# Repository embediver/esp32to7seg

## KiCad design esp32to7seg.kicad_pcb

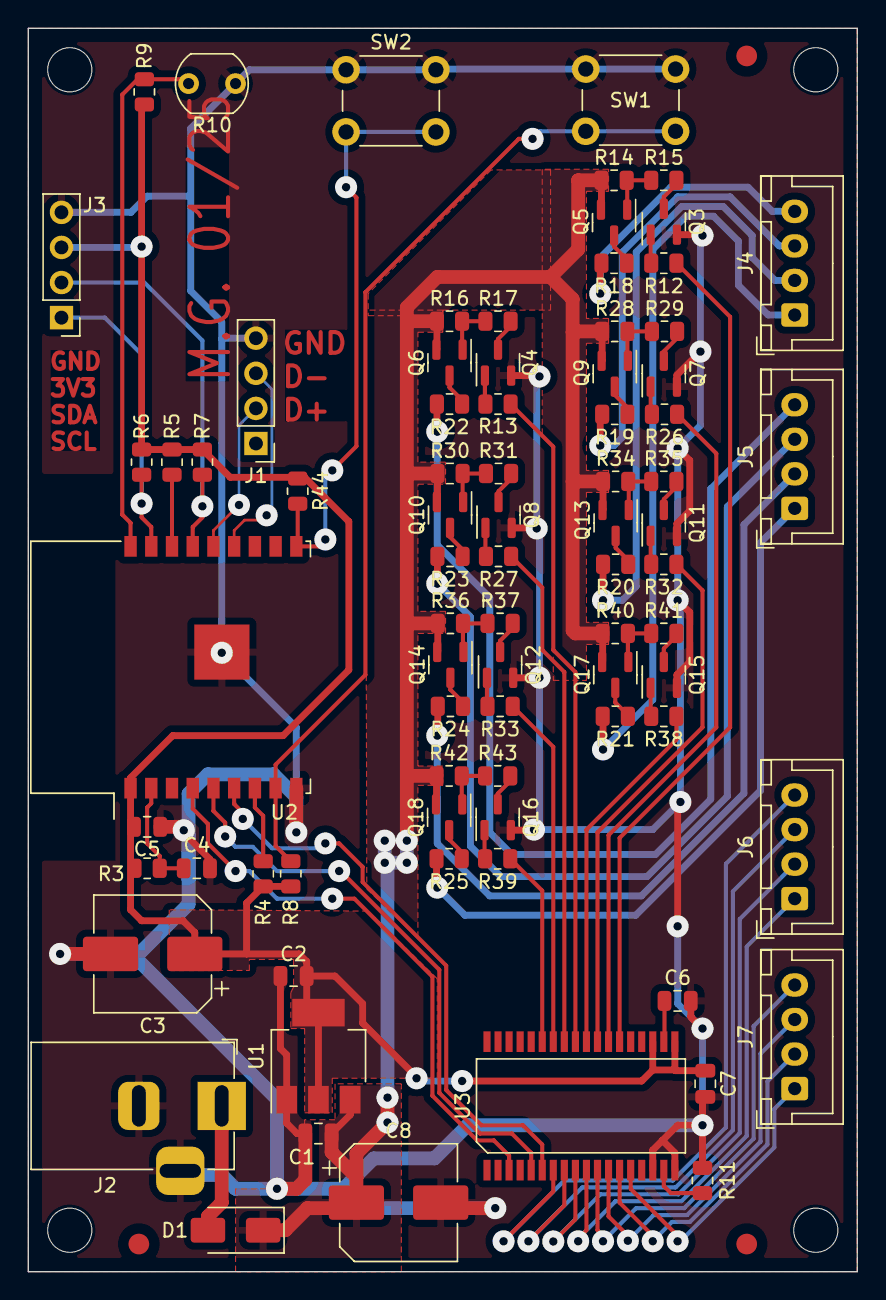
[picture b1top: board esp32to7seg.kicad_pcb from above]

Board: 2 copper layers, 60.0 x 90.0 mm, 86 parts (0 on the bottom side), 75 nets.

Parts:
C1, C2, C5, C7: 100n; C_0805_2012Metric
C3, C8: 220u; CP_Elec_8x6.2
C4: 1u; C_0805_2012Metric
C6: 22p; C_0805_2012Metric
D1: D_Schottky; D_SMA
FID1, FID2, FID3: Fiducial; Fiducial_1.5mm_Mask3mm
H1, H2, H3, H4: MountingHole; MountingHole_3.2mm_M3_DIN965
J1: Conn_01x04_Pin; PinHeader_1x04_P2.54mm_Vertical
J2: Barrel_Jack_Switch; BarrelJack_Horizontal
J3: Conn_01x04; PinHeader_1x04_P2.54mm_Vertical
J4, J5, J6, J7: Conn_01x04_Pin; JST_XH_B4B-XH-A_1x04_P2.50mm_Vertical
Q3, Q4, Q7, Q8, Q11, Q12, Q15, Q16: BC817; SOT-23
Q5, Q6, Q9, Q10, Q13, Q14, Q17, Q18: BC807; SOT-23
R3, R4, R5, R6, R7, R8, R12, R13, R14, R16, R26, R27, R28, R30, R32, R33, R34, R36, R38, R39, R40, R42, R44: 10k; R_0805_2012Metric
R9: tbd; R_0805_2012Metric
R10: LDR07; R_LDR_5.1x4.3mm_P3.4mm_Vertical
R11: 56k; R_0805_2012Metric
R15, R17, R29, R31, R35, R37, R41, R43: 1k; R_0805_2012Metric
R18, R19, R20, R21, R22, R23, R24: 150R; R_0805_2012Metric
R25: 350R; R_0805_2012Metric
SW1, SW2: SW_Push; SW_PUSH_6mm
U1: LT1117-3.3; SOT-223-3_TabPin2
U2: ESP32-C3-WROOM-02; ESP-WROOM-02
U3: MAX6954; SOIC-36

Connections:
+3V3: C2.1, C3.1, C5.1, C7.1, J3.3, R3.2, R4.1, R5.1, R6.1, R7.1, R8.1, R9.1, R44.1, U1.2 (VO), U2.1 (VDD), U3.19 (VIN), U3.21 (VIN)
+9V: C1.1, C8.1, D1.1 (K), Q5.2 (E), Q6.2 (E), Q9.2 (E), Q10.2 (E), Q13.2 (E), Q14.2 (E), Q17.2 (E), Q18.2 (E), R14.1, R16.1, R28.1, R30.1, R34.1, R36.1, R40.1, R42.1, U1.3 (VI)
/9V_IN: D1.2 (A), J2.1
/ADC: R9.2, R10.1, U2.18 (IO0)
/BOOT_SEL: R8.2, SW1.2, U2.8 (IO9)
/BUTTON2: R44.2, SW2.2, U2.10 (IO10)
/EN: C4.1, R3.1, U2.2 (EN)
/Led Driver/CLK: U2.5 (IO6), U3.5 (CLK)
/Led Driver/DIG0: J6.4, U3.7 (O0)
/Led Driver/DIG1: J6.3, U3.8 (O1)
/Led Driver/DIG2: J6.2, U3.9 (O2)
/Led Driver/DIG3: J6.1, U3.10 (O3)
/Led Driver/DIG4: J7.4, U3.11 (O4)
/Led Driver/DIG5: J7.3, U3.12 (O5)
/Led Driver/DIG6: J7.2, U3.13 (O6)
/Led Driver/DIG7: J7.1, U3.14 (O7)
/Led Driver/DIN: U2.6 (IO7), U3.6 (DIN)
/Led Driver/SEG_A: R12.1, U3.24 (O11)
/Led Driver/SEG_A_LD: Q5.3 (C), R18.1
/Led Driver/SEG_B: R26.1, U3.25 (O12)
/Led Driver/SEG_B_LD: Q9.3 (C), R19.1
/Led Driver/SEG_C: R32.1, U3.26 (O13)
/Led Driver/SEG_C_LD: Q13.3 (C), R20.1
/Led Driver/SEG_D: R38.1, U3.27 (O14)
/Led Driver/SEG_DP: R39.1, U3.31 (O18)
/Led Driver/SEG_DP_LD: Q18.3 (C), R25.1
/Led Driver/SEG_D_LD: Q17.3 (C), R21.1
/Led Driver/SEG_E: R13.2, U3.28 (O15)
/Led Driver/SEG_E_LD: Q6.3 (C), R22.1
/Led Driver/SEG_F: R27.1, U3.29 (O16)
/Led Driver/SEG_F_LD: Q10.3 (C), R23.1
/Led Driver/SEG_G: R33.1, U3.30 (O17)
/Led Driver/SEG_G_LD: Q14.3 (C), R24.1
/Led Driver/~CS: U2.4 (IO5), U3.3 (~CS)
/SCL: J3.1, R6.2, U2.17 (IO1)
/SDA: J3.2, R7.2, U2.15 (IO3)
/USB+: J1.2, U2.14 (IO19)
/USB-: J1.3, U2.13 (IO18)
GND: C1.2, C2.2, C3.2, C4.2, C5.2, C6.2, C7.2, C8.2, J1.4, J2.2, J2.3, J3.4, Q3.2 (E), Q4.2 (E), Q7.2 (E), Q8.2 (E), Q11.2 (E), Q12.2 (E), Q15.2 (E), Q16.2 (E), R10.2, R11.2, SW1.1, SW2.1, U1.1 (GND), U2.9 (GND), U2.19 (GND), U3.16 (GND), U3.18 (GND)
unnamed: J4.1, R21.2
unnamed: J4.2, R20.2
unnamed: J4.3, R19.2
unnamed: J4.4, R18.2
unnamed: J5.1, R25.2
unnamed: J5.2, R24.2
unnamed: J5.3, R23.2
unnamed: J5.4, R22.2
unnamed: Q3.1 (B), R12.2
unnamed: Q3.3 (C), R15.2
unnamed: Q4.1 (B), R13.1
unnamed: Q4.3 (C), R17.2
unnamed: Q5.1 (B), R14.2, R15.1
unnamed: Q6.1 (B), R16.2, R17.1
unnamed: Q7.1 (B), R26.2
unnamed: Q7.3 (C), R29.2
unnamed: Q8.1 (B), R27.2
unnamed: Q8.3 (C), R31.2
unnamed: Q9.1 (B), R28.2, R29.1
unnamed: Q10.1 (B), R30.2, R31.1
unnamed: Q11.1 (B), R32.2
unnamed: Q11.3 (C), R35.2
unnamed: Q12.1 (B), R33.2
unnamed: Q12.3 (C), R37.2
unnamed: Q13.1 (B), R34.2, R35.1
unnamed: Q14.1 (B), R36.2, R37.1
unnamed: Q15.1 (B), R38.2
unnamed: Q15.3 (C), R41.2
unnamed: Q16.1 (B), R39.2
unnamed: Q16.3 (C), R43.2
unnamed: Q17.1 (B), R40.2, R41.1
unnamed: Q18.1 (B), R42.2, R43.1
unnamed: R5.2, U2.16 (IO2)
unnamed: R4.2, U2.7 (IO8)
unnamed: R11.1, U3.17 (ISET)
unnamed: C6.1, U3.20 (OSC)

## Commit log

2023-10-25 Initial commit.
2023-10-26 Route this stuff...
2023-10-26 Fix DRC violations.
2023-10-26 Add 3v3 pin to i2c header.
2025-01-09 Multiple improvements
